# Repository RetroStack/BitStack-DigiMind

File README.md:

# DigiMind

As part of an introduction in digital electronics workshop at VCF SW 2024, I prepared this design of a Masterm\*nd like game to teach digital electronics.

## Latest Files

In the "Latest" folder, you'll find the most up-to-date design files, including:

- Gerber files suitable for popular online PCB manufacturers like [PCBWay](/Latest/DigiMind_Gerber_PCBWay.zip) and [JLCPCB](/Latest/DigiMind_Gerber_JLCPCB.zip). Most manufacturers should be fine with either.
- A Bill of Materials (BOM) in both [CSV](/Latest/DigiMind_BOM.csv) and [PDF](/Latest/DigiMind_BOM.pdf) formats.
- The [full schematics](/Latest/DigiMind_Schematics.pdf) of the board.

## Implementation

The board has been implemented using KiCAD 8. The KiCAD project files are included in this repository.

## How to Play

There are two players for this game:

- A person guessing the master code
- A person defining the master code

Before starting the game, the person defining the master code hits the "Reset" button to reset the game's state. Then, they enter the code using the DIP switches labeled "Master." When completed, the "Set" button must be pushed to set the master code. After that, the master code can be cleared from the DIP switches as it has been read into the memory.

As soon as the "Set" button is pressed, a timer labeled "Timer" starts running down. When the last light turns off, the game is over (if the master code was not found). The potentiometer labeled "Speed" can increase the time a player has to guess the master code.

The guesser needs to enter a code into the DIP switch on the other side, labeled "Guess." The "Set" button right next to it can be pressed to trigger a guess attempt. Each attempt is recognized and counted up with the "Tries" lights. When reaching a binary 8, the game is over.

In either case, when the time runs out or when 8 guesses have been made and the guess was wrong, the "Game Over" light indicates the game is over. This light will turn on regardless of whether the master code was found or not (to simplify the logic). What is important is the "=" light that indicates if the guess was correct.

If the guess was wrong, the board indicates if the master code is higher or lower than the entered guess. These indicators are labeled "<" and ">".

### Known Issues

Some decisions were made to keep the diagram somewhat readable for beginners. For example, the "Game Over" light will turn on regardless if the guess was found or not. There is also an issue when entering guesses where a bouncing of the "Set" button causes multiple guesses to register. This can be fixed by a debouncing circuit.

## Bill of Materials (BOM)

Below is a list of materials needed to assemble the PCB.

| Reference                 | Qty | Description        | Footprint                                                      | Datasheet                                  |
| ------------------------- | --- | ------------------ | -------------------------------------------------------------- | ------------------------------------------ |
| C1                        | 1   | 10uF               | Capacitor_THT:C_Disc_D5.1mm_W3.2mm_P5.00mm                     | ~                                          |
| C2                        | 1   | 0.01uF             | Capacitor_THT:C_Disc_D5.1mm_W3.2mm_P5.00mm                     | ~                                          |
| C3,C4,C5,C6,C7,C8,C9      | 7   | C                  | Capacitor_THT:C_Disc_D5.1mm_W3.2mm_P5.00mm                     | ~                                          |
| D1                        | 1   | Green              | LED_THT:LED_D5.0mm                                             | ~                                          |
| D2,D3                     | 2   | Yellow             | LED_THT:LED_D5.0mm                                             | ~                                          |
| D4,D5,D6,D7,D8,D9,D10,D11 | 8   | Red                | LED_THT:LED_D5.0mm                                             | ~                                          |
| J1                        | 1   | Barrel_Jack_Switch | Connector_BarrelJack:BarrelJack_Horizontal                     | ~                                          |
| R1,R5,R6                  | 3   | R                  | Resistor_THT:R_Axial_DIN0207_L6.3mm_D2.5mm_P10.16mm_Horizontal | ~                                          |
| R2,R15,R16                | 3   | 1k                 | Resistor_THT:R_Axial_DIN0207_L6.3mm_D2.5mm_P10.16mm_Horizontal | ~                                          |
| RN1                       | 1   | R_Network04        | Resistor_THT:R_Array_SIP5                                      | http://www.vishay.com/docs/31509/csc.pdf   |
| RN2,RN3                   | 2   | R_Network03        | Resistor_THT:R_Array_SIP4                                      | http://www.vishay.com/docs/31509/csc.pdf   |
| RV1                       | 1   | 1M                 | Potentiometer_THT:Potentiometer_Bourns_3386P_Vertical          | ~                                          |
| SW1,SW2                   | 2   | SW_DIP_x04         | Package_DIP:DIP-8_W7.62mm                                      | ~                                          |
| SW3,SW4,SW5               | 3   | SW_Push            | RetroStackLibrary:SW_SPST_Push                                 | ~                                          |
| U2                        | 1   | 74LS161            | Package_DIP:DIP-16_W7.62mm                                     | http://www.ti.com/lit/gpn/sn74LS161        |
| U3                        | 1   | 74LS174            | Package_DIP:DIP-16_W7.62mm                                     | http://www.ti.com/lit/gpn/sn74LS174        |
| U4                        | 1   | 74LS85             | Package_DIP:DIP-16_W7.62mm                                     | http://www.ti.com/lit/gpn/sn74LS85         |
| U5                        | 1   | 74LS175            | Package_DIP:DIP-16_W7.62mm                                     | http://www.ti.com/lit/gpn/sn74LS175        |
| U6                        | 1   | 74LS08             | Package_DIP:DIP-14_W7.62mm                                     | http://www.ti.com/lit/gpn/sn74LS08         |
| U7                        | 1   | 74LS194            | Package_DIP:DIP-16_W7.62mm                                     | http://www.ti.com/lit/gpn/sn74LS194        |
| U8                        | 1   | 74LS02             |                                                                | http://www.ti.com/lit/gpn/sn74ls02         |
| U10                       | 1   | NA555P             | Package_DIP:DIP-8_W7.62mm                                      | http://www.ti.com/lit/ds/symlink/ne555.pdf |

## RetroStack Libraries

To work with this KiCAD project, you'll need the RetroStack libraries for KiCAD. Please [follow this link](https://www.github.com/RetroStack/KiCAD-Libraries) to access and install these libraries.

## Support this Project

RetroStack is passionate about exploring and preserving the legacy of older computer systems. BitStack is a sub-project of RetroStack, focusing on education in digital electronics. My work involves creating detailed documentation and videos to share the knowledge. I am also dedicated to reviving these classic systems by reimplementing them and offering replacement parts at no cost. If you're keen on supporting this unique project, I invite you to visit my [Patreon page](https://www.patreon.com/RetroStack). Your support would be immensely valuable and greatly appreciated!

## License

This project is licensed under the MIT License - see the [LICENSE](LICENSE) file for details.

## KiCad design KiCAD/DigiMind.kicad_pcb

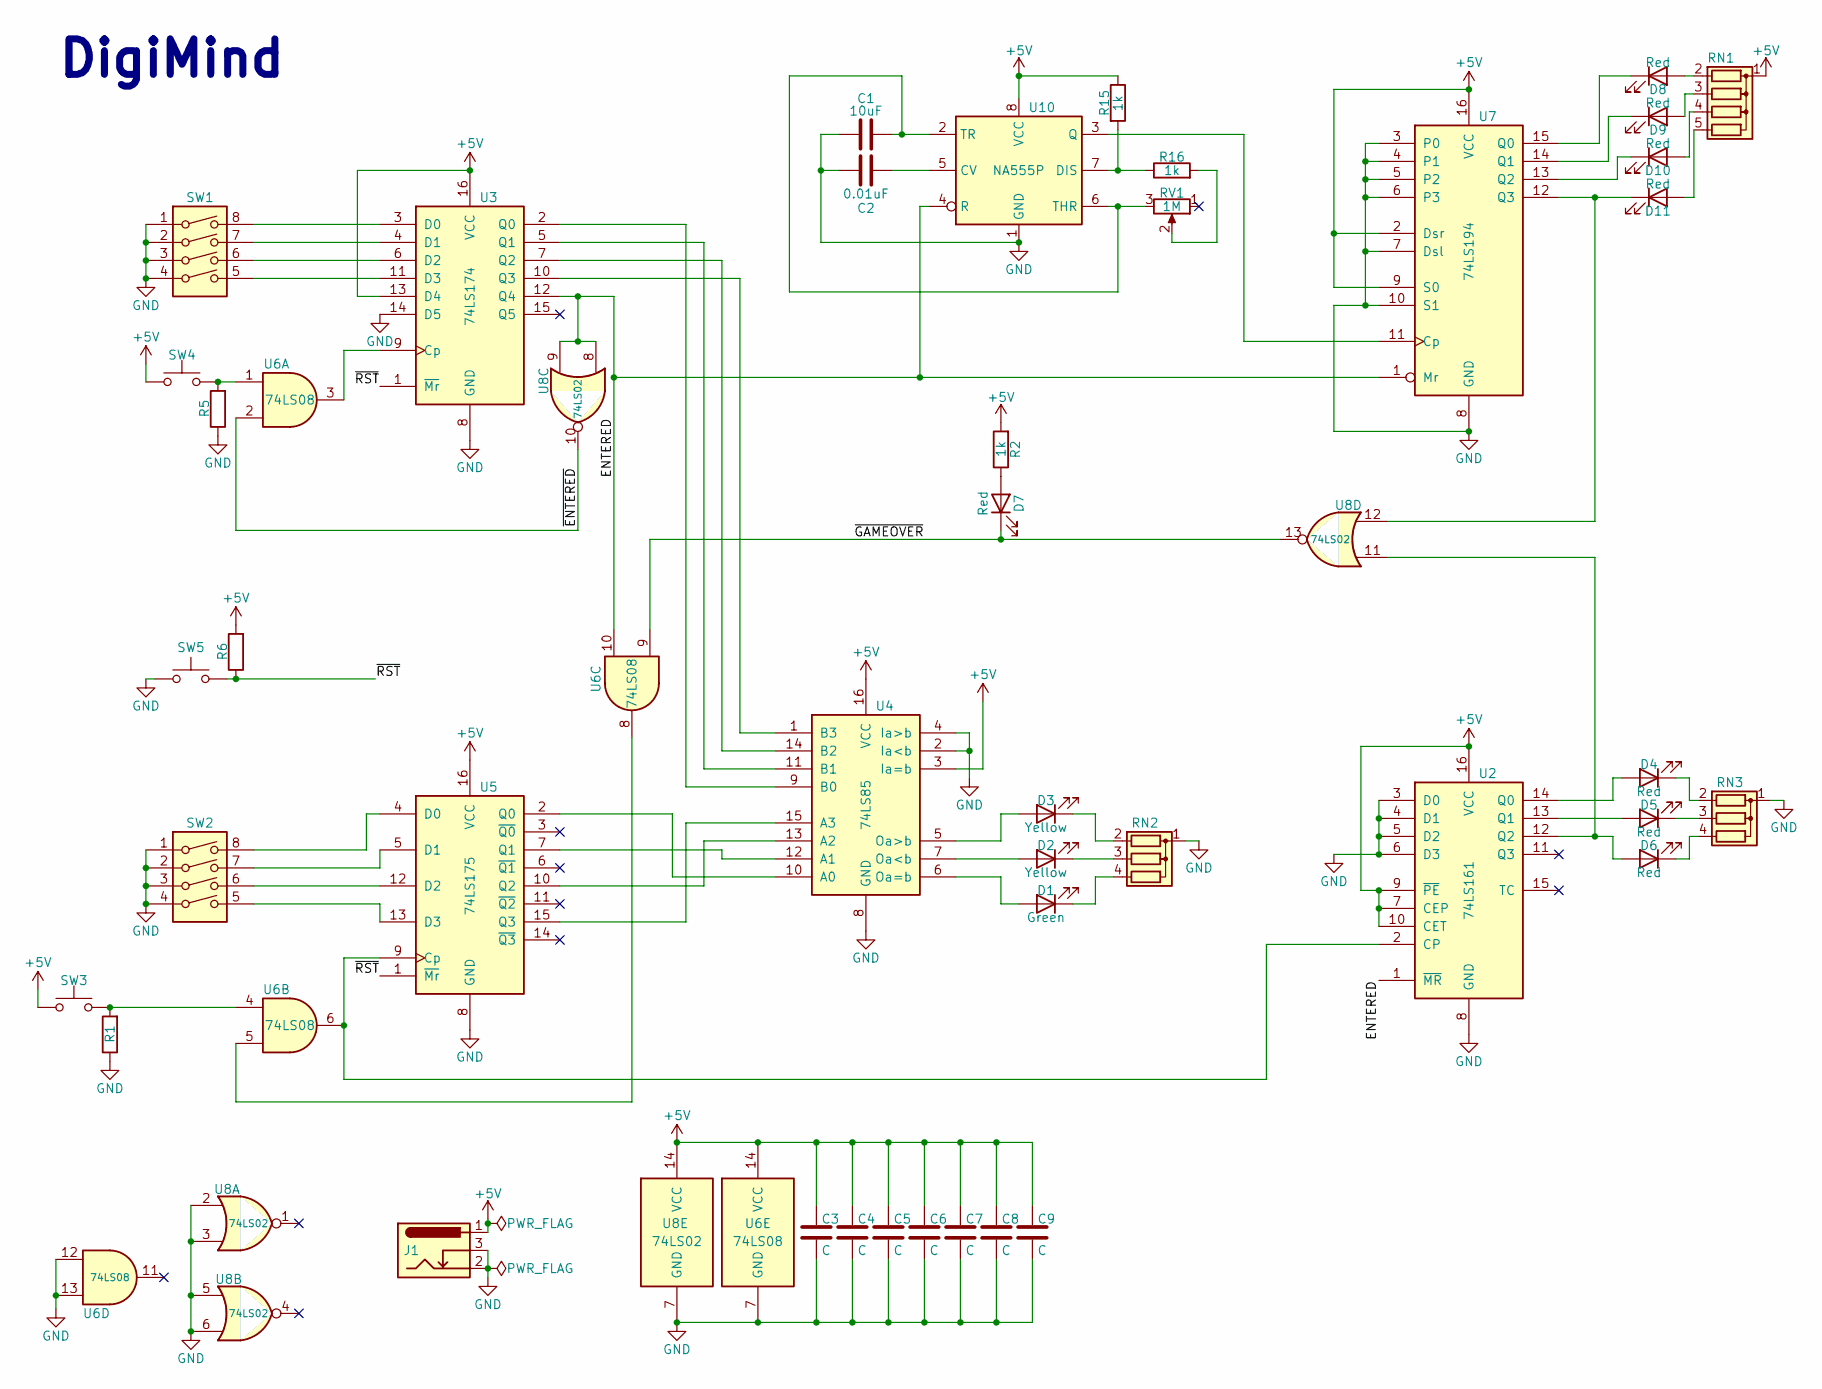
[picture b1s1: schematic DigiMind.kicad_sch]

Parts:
C1: 10uF; C_Disc_D5.1mm_W3.2mm_P5.00mm
C2: 0.01uF; C_Disc_D5.1mm_W3.2mm_P5.00mm
C3, C4, C5, C6, C7, C8, C9: C; C_Disc_D5.1mm_W3.2mm_P5.00mm
D1: Green; LED_D5.0mm
D2, D3: Yellow; LED_D5.0mm
D4, D5, D6, D7, D8, D9, D10, D11: Red; LED_D5.0mm
J1: Barrel_Jack_Switch; BarrelJack_Horizontal
R1, R5, R6: R; R_Axial_DIN0207_L6.3mm_D2.5mm_P10.16mm_Horizontal
R2, R15, R16: 1k; R_Axial_DIN0207_L6.3mm_D2.5mm_P10.16mm_Horizontal
RN1: R_Network04; R_Array_SIP5
RN2, RN3: R_Network03; R_Array_SIP4
RV1: 1M; Potentiometer_Bourns_3386P_Vertical
SW1, SW2: SW_DIP_x04; DIP-8_W7.62mm
SW3, SW4, SW5: SW_Push; SW_SPST_Push
U2: 74LS161; DIP-16_W7.62mm
U3: 74LS174; DIP-16_W7.62mm
U4: 74LS85; DIP-16_W7.62mm
U5: 74LS175; DIP-16_W7.62mm
U6: 74LS08; DIP-14_W7.62mm
U7: 74LS194; DIP-16_W7.62mm
U8: 74LS02
U10: NA555P; DIP-8_W7.62mm

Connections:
+5V: C3.1, C4.1, C5.1, C6.1, C7.1, C8.1, C9.1, J1.1, R2.2, R6.2, R15.1, RN1.1 (common), SW3.1, SW4.1, U2.7 (CEP), U2.9 (~PE), U2.10 (CET), U2.16 (VCC), U3.13 (D4), U3.16 (VCC), U4.3 (Ia=b), U4.16 (VCC), U5.16 (VCC), U6.14 (VCC), U7.2 (Dsr), U7.9 (S0), U7.16 (VCC), U8.14 (VCC), U10.8 (VCC); also elsewhere on the board
/ENTERED: U2.1 (~MR), U3.12 (Q4), U6.10, U7.1 (Mr), U8.8, U8.9, U10.4 (R); also elsewhere on the board
/~ENTERED: U6.2, U8.10; also elsewhere on the board
/~GAMEOVER: D7.1 (K), U6.9, U6.11, U8.13
/~RST: R6.1, SW5.2, U3.1 (~Mr), U5.1 (~Mr)
unnamed: D1.2 (A), U4.6 (Oa=b)
unnamed: D1.1 (K), RN2.4 (R3)
unnamed: D2.2 (A), U4.7 (Oa<b)
unnamed: D2.1 (K), RN2.3 (R2)
unnamed: D3.2 (A), U4.5 (Oa>b)
unnamed: D3.1 (K), RN2.2 (R1)
unnamed: D4.2 (A), U2.14 (Q0)
unnamed: D4.1 (K), RN3.2 (R1)
unnamed: D5.2 (A), U2.13 (Q1)
unnamed: D5.1 (K), RN3.3 (R2)
unnamed 15: D6.2 (A), U2.12 (Q2), U8.11; also elsewhere on the board
unnamed: D6.1 (K), RN3.4 (R3)
unnamed: D7.2 (A), R2.1
unnamed: D8.2 (A), RN1.2 (R1)
unnamed: D8.1 (K), U7.15 (Q0)
unnamed: D9.2 (A), RN1.3 (R2)
unnamed: D9.1 (K), U7.14 (Q1)
unnamed: D10.2 (A), RN1.4 (R3)
unnamed: D10.1 (K), U7.13 (Q2)
unnamed: D11.2 (A), RN1.5 (R4)
unnamed 25: D11.1 (K), U7.12 (Q3), U8.12; also elsewhere on the board
unnamed: R1.2, SW3.2, U6.4
unnamed: R5.2, SW4.2, U6.1
unnamed: R16.2, RV1.2
unnamed: U2.2 (CP), U5.9 (Cp), U6.6
unnamed: U3.9 (Cp), U6.3
unnamed: SW1.8, U3.3 (D0)
unnamed: SW1.7, U3.4 (D1)
unnamed: SW1.6, U3.6 (D2)
unnamed: SW1.5, U3.11 (D3)
unnamed: U3.2 (Q0), U4.9 (B0)
unnamed: U3.5 (Q1), U4.11 (B1)
unnamed: U3.7 (Q2), U4.14 (B2)
unnamed: U3.10 (Q3), U4.1 (B3)
unnamed: U4.10 (A0), U5.2 (Q0)
unnamed: U4.12 (A1), U5.7 (Q1)
unnamed: U4.13 (A2), U5.10 (Q2)
unnamed: U4.15 (A3), U5.15 (Q3)
unnamed: SW2.8, U5.4 (D0)
unnamed: SW2.7, U5.5 (D1)
unnamed: SW2.6, U5.12 (D2)
unnamed: SW2.5, U5.13 (D3)
unnamed: U6.5, U6.8
unnamed: C2.2, U10.5 (CV)
unnamed: R15.2, R16.1, U10.7 (DIS)
unnamed: U7.11 (Cp), U10.3 (Q)
unnamed: C1.2, RV1.3, U10.2 (TR), U10.6 (THR)

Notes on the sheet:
DigiMind

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
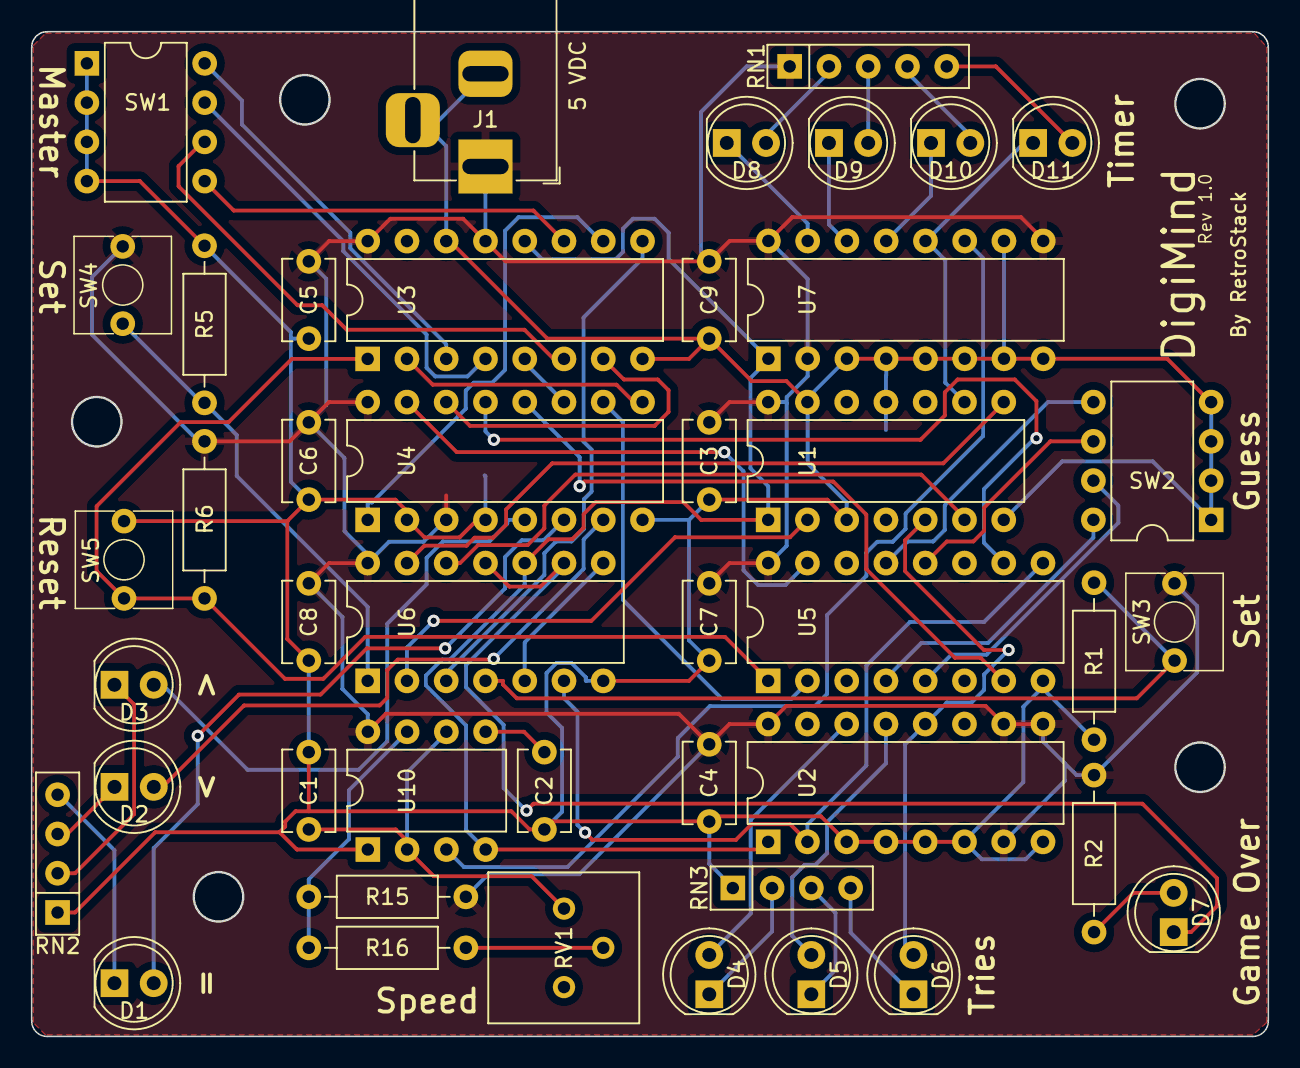
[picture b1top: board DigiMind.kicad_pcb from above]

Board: 2 copper layers, 80.0 x 64.9 mm, 44 parts (0 on the bottom side), 55 nets.

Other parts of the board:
U1: 74LS04; DIP-14_W7.62mm

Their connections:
+5V: U1.14 (VCC); also elsewhere on the board
/ENTERED: U1.1; also elsewhere on the board
/~ENTERED: U1.2; also elsewhere on the board
unnamed 15: U1.5; also elsewhere on the board
unnamed 25: U1.9; also elsewhere on the board

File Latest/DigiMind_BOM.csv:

"Reference","Value","Datasheet","Footprint","Qty","DNP"
"C1","10uF","~","Capacitor_THT:C_Disc_D5.1mm_W3.2mm_P5.00mm","1",""
"C2","0.01uF","~","Capacitor_THT:C_Disc_D5.1mm_W3.2mm_P5.00mm","1",""
"C3,C4,C5,C6,C7,C8,C9","C","~","Capacitor_THT:C_Disc_D5.1mm_W3.2mm_P5.00mm","7",""
"D1","Green","~","LED_THT:LED_D5.0mm","1",""
"D2,D3","Yellow","~","LED_THT:LED_D5.0mm","2",""
"D4,D5,D6,D7,D8,D9,D10,D11","Red","~","LED_THT:LED_D5.0mm","8",""
"J1","Barrel_Jack_Switch","~","Connector_BarrelJack:BarrelJack_Horizontal","1",""
"R1,R5,R6","R","~","Resistor_THT:R_Axial_DIN0207_L6.3mm_D2.5mm_P10.16mm_Horizontal","3",""
"R2,R15,R16","1k","~","Resistor_THT:R_Axial_DIN0207_L6.3mm_D2.5mm_P10.16mm_Horizontal","3",""
"RN1","R_Network04","http://www.vishay.com/docs/31509/csc.pdf","Resistor_THT:R_Array_SIP5","1",""
"RN2,RN3","R_Network03","http://www.vishay.com/docs/31509/csc.pdf","Resistor_THT:R_Array_SIP4","2",""
"RV1","1M","~","Potentiometer_THT:Potentiometer_Bourns_3386P_Vertical","1",""
"SW1,SW2","SW_DIP_x04","~","Package_DIP:DIP-8_W7.62mm","2",""
"SW3,SW4,SW5","SW_Push","~","RetroStackLibrary:SW_SPST_Push","3",""
"U2","74LS161","http://www.ti.com/lit/gpn/sn74LS161","Package_DIP:DIP-16_W7.62mm","1",""
"U3","74LS174","http://www.ti.com/lit/gpn/sn74LS174","Package_DIP:DIP-16_W7.62mm","1",""
"U4","74LS85","http://www.ti.com/lit/gpn/sn74LS85","Package_DIP:DIP-16_W7.62mm","1",""
"U5","74LS175","http://www.ti.com/lit/gpn/sn74LS175","Package_DIP:DIP-16_W7.62mm","1",""
"U6","74LS08","http://www.ti.com/lit/gpn/sn74LS08","Package_DIP:DIP-14_W7.62mm","1",""
"U7","74LS194","http://www.ti.com/lit/gpn/sn74LS194","Package_DIP:DIP-16_W7.62mm","1",""
"U8","74LS02","http://www.ti.com/lit/gpn/sn74ls02","","1",""
"U10","NA555P","http://www.ti.com/lit/ds/symlink/ne555.pdf","Package_DIP:DIP-8_W7.62mm","1",""
